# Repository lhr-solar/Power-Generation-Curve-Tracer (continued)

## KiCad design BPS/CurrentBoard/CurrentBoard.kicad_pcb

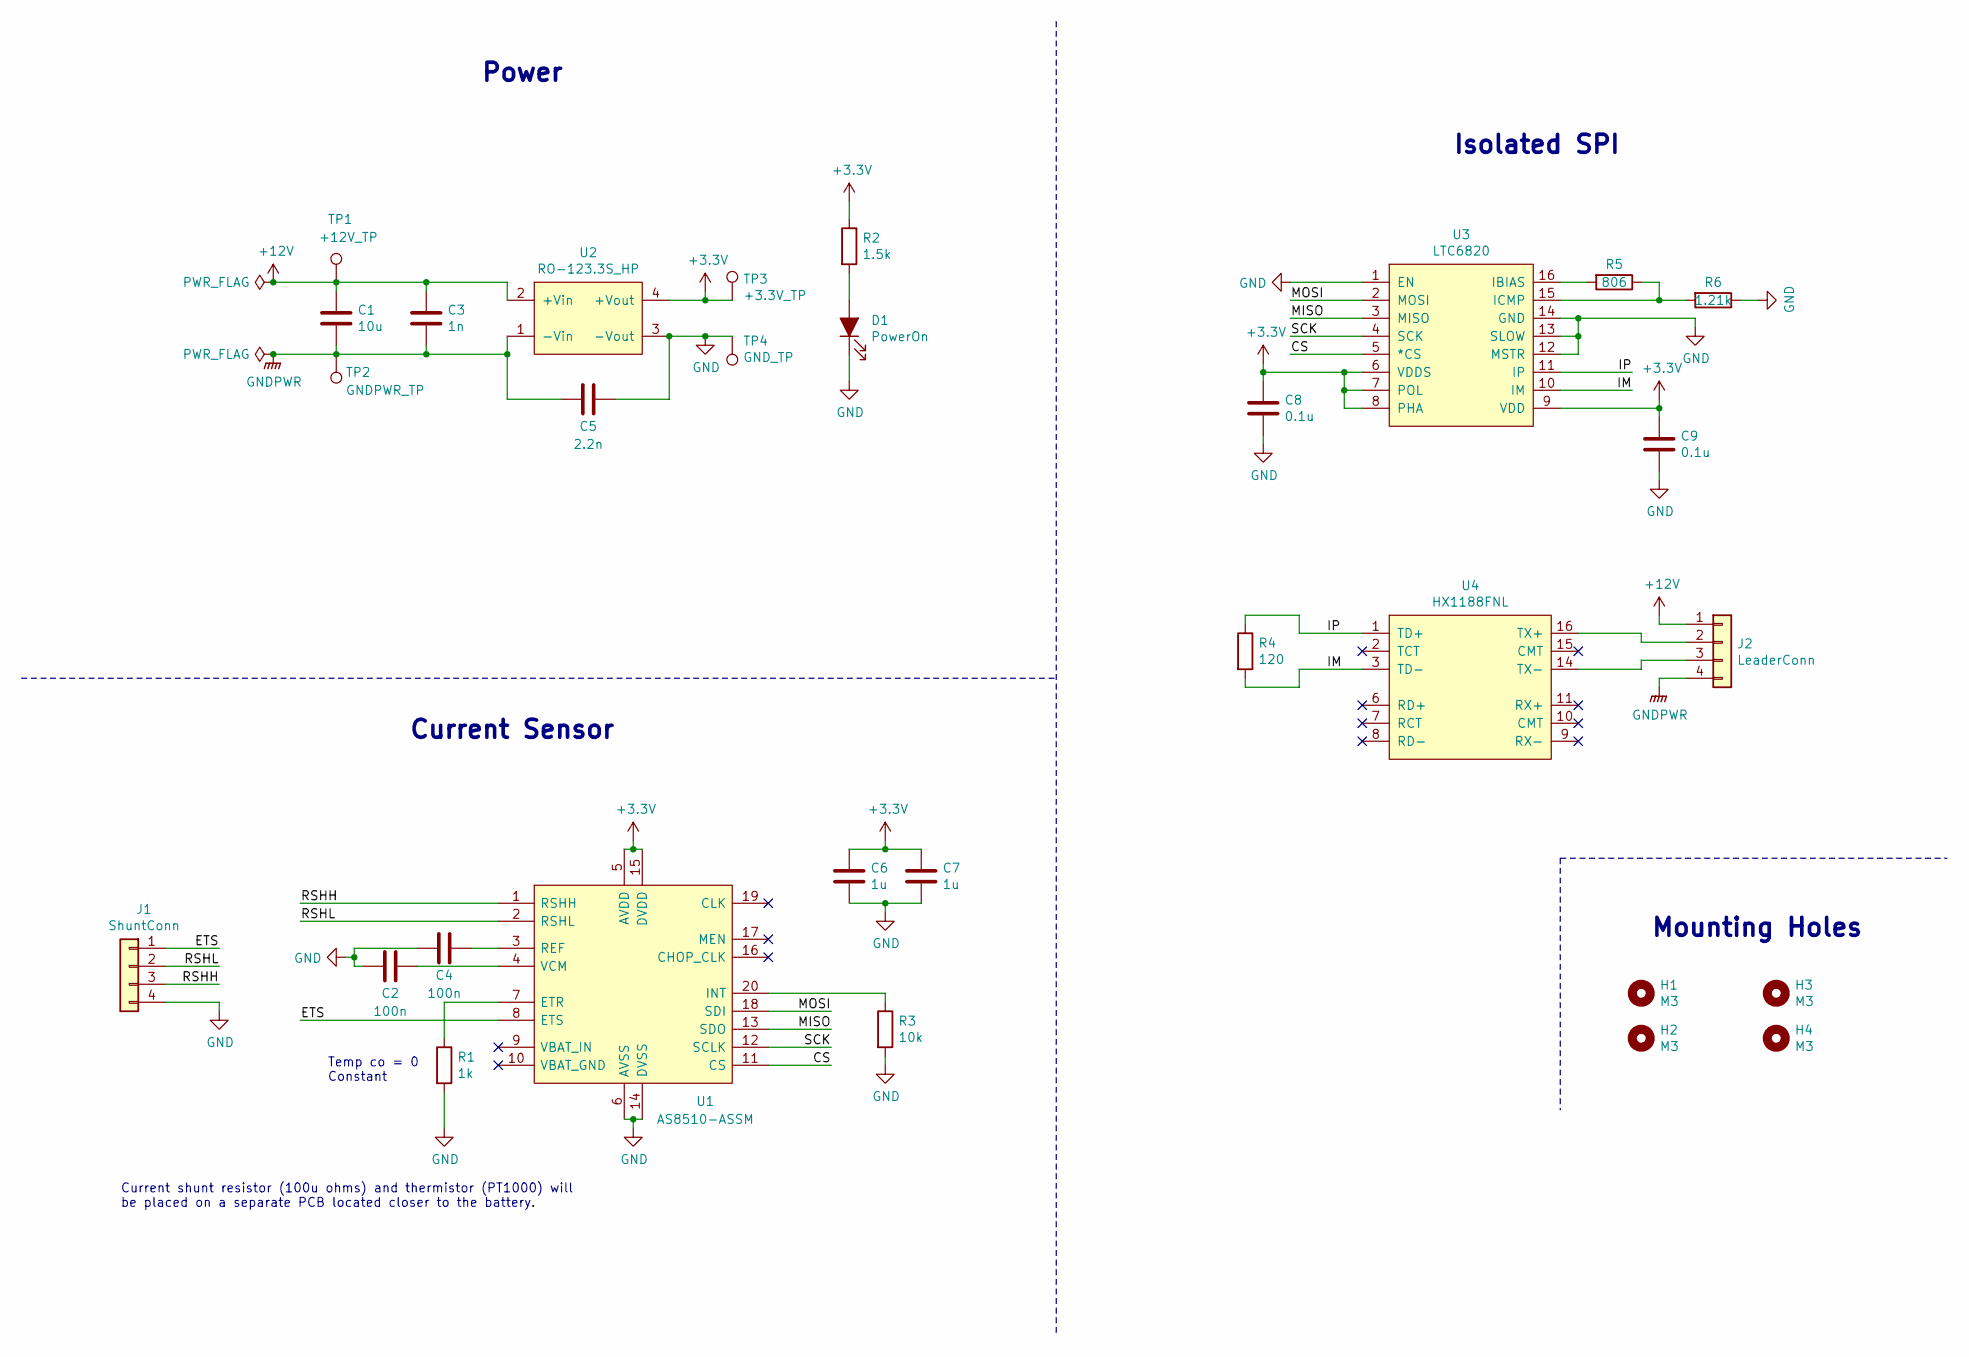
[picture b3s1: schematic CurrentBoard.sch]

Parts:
C1: 10u; C_2220_5750Metrix
C2, C4: 100n; C_0805_2012Metric
C3: 1n; C_0805_2012Metric
C5: 2.2n; C_0805_2012Metric
C6, C7: 1u; C_0805_2012Metric
C8, C9: 0.1u; C_0805_2012Metric
D1: PowerOn; LED_0805_2012Metric
H1, H2, H3, H4: M3; MountingHole_3mm
J1: ShuntConn; Molex_Micro-Fit_3.0_43650-0415_1x04_P3.00mm_Vertical
J2: LeaderConn; Molex_Micro-Fit_3.0_43650-0415_1x04_P3.00mm_Vertical
R1: 1k; R_0805_2012Metric
R2: 1.5k; R_0805_2012Metric
R3: 10k; R_0805_2012Metric
R4: 120; R_0805_2012Metric
R5: 806; R_0805_2012Metric
R6: 1.21k; R_0805_2012Metric
TP1: +12V_TP; TestPoint_Keystone_5005-5009_Compact
TP2: GNDPWR_TP; TestPoint_Keystone_5005-5009_Compact
TP3: +3.3V_TP; TestPoint_Keystone_5005-5009_Compact
TP4: GND_TP; TestPoint_Keystone_5005-5009_Compact
U1: AS8510-ASSM; Manufacturer_Part_Number AS8510-ASSM; Mouser Part Number 985-AS8510-ASSM
U2: RO-123.3S_HP; RI3_DC_Converter
U3: LTC6820; MSOP-16_3x4mm_P0.5mm
U4: HX1188FNL; HXXXX

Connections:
+3V3: C6.1, C7.1, C8.1, C9.1, R2.1, TP3.1, U1.5 (AVDD), U1.15 (DVDD), U2.4 (+Vout), U3.6 (VDDS), U3.7 (POL), U3.8 (PHA), U3.9 (VDD)
+12V: C1.1, C3.1, J2.1, TP1.1, U2.2 (+Vin)
/CS: U1.11 (CS), U3.5 (*CS)
/ETS: J1.1, U1.8 (ETS)
/IM: R4.2, U3.10 (IM), U4.3 (TD-)
/IP: R4.1, U3.11 (IP), U4.1 (TD+)
/MISO: U1.13 (SDO), U3.3 (MISO)
/MOSI: U1.18 (SDI), U3.2 (MOSI)
/RSHH: J1.3, U1.1 (RSHH)
/RSHL: J1.2, U1.2 (RSHL)
/SCK: U1.12 (SCLK), U3.4 (SCK)
GND: C2.2, C4.1, C5.2, C6.2, C7.2, C8.2, C9.2, D1.1 (K), J1.4, R1.2, R3.2, R6.1, TP4.1, U1.6 (AVSS), U1.14 (DVSS), U2.3 (-Vout), U3.1 (EN), U3.12 (MSTR), U3.13 (SLOW), U3.14 (GND)
GNDPWR: C1.2, C3.2, C5.1, J2.4, TP2.1, U2.1 (-Vin)
unnamed: C2.1, U1.4 (VCM)
unnamed: C4.2, U1.3 (REF)
unnamed: D1.2 (A), R2.2
unnamed: J2.2, U4.16 (TX+)
unnamed: J2.3, U4.14 (TX-)
unnamed: R1.1, U1.7 (ETR)
unnamed: R3.1, U1.20 (INT)
unnamed: R5.1, R6.2, U3.15 (ICMP)
unnamed: R5.2, U3.16 (IBIAS)

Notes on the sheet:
Current shunt resistor (100u ohms) and thermistor (PT1000) will be placed on a separate PCB located closer to the battery.
Temp co = 0 Constant
Isolated SPI
Current Sensor
Mounting Holes
Power

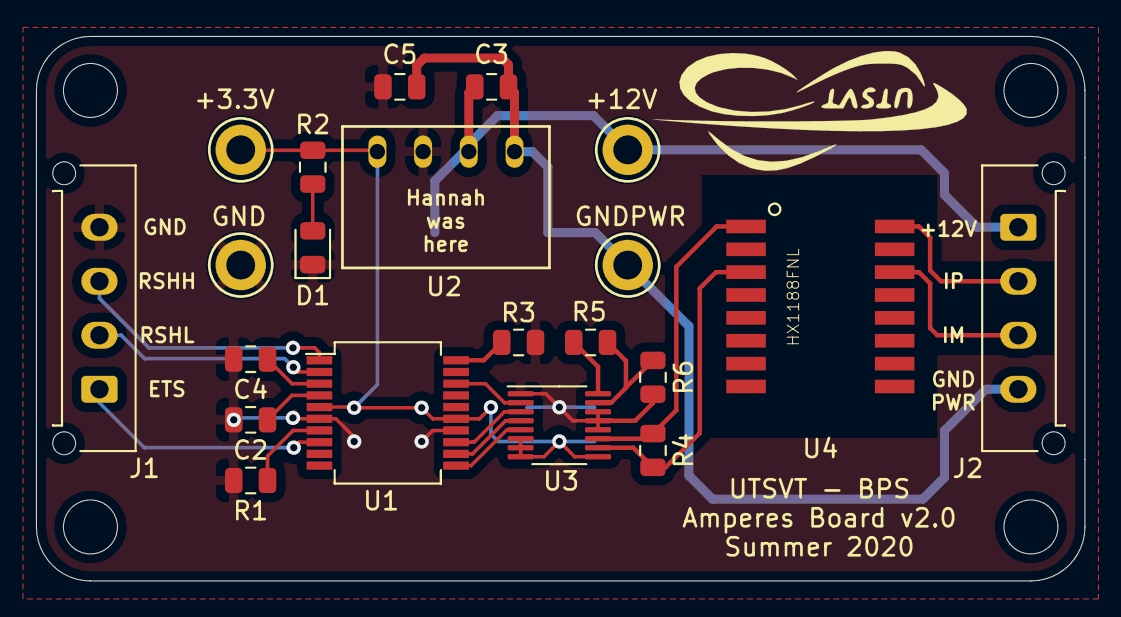
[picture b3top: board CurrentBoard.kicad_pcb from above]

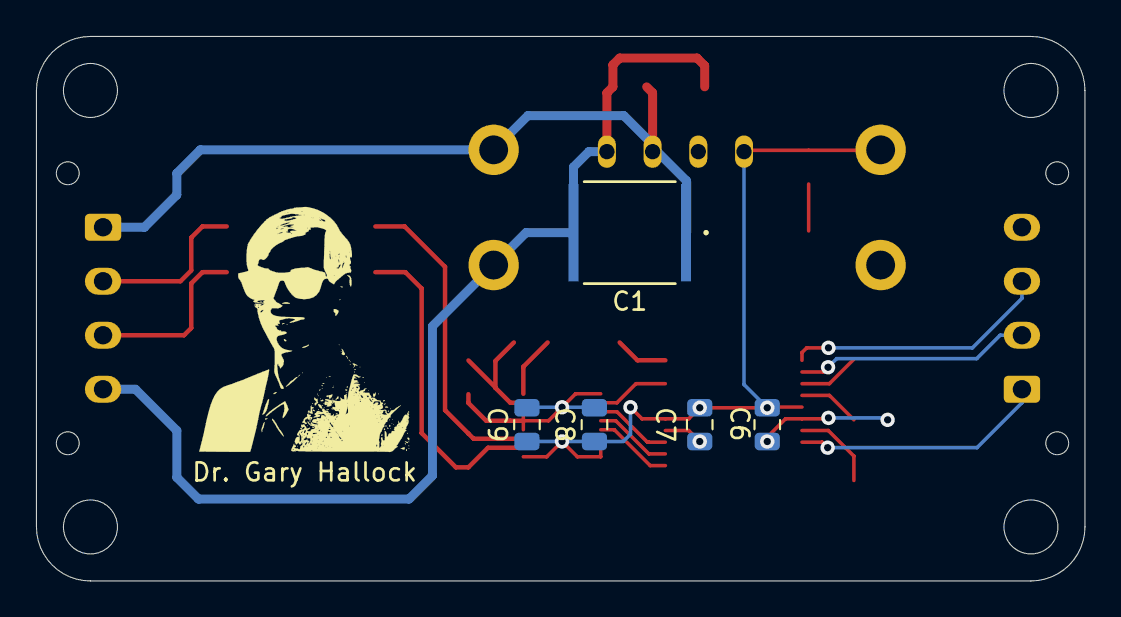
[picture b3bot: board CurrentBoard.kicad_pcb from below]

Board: 2 copper layers, 58.2 x 30.2 mm, 30 parts (5 on the bottom side), 22 nets.

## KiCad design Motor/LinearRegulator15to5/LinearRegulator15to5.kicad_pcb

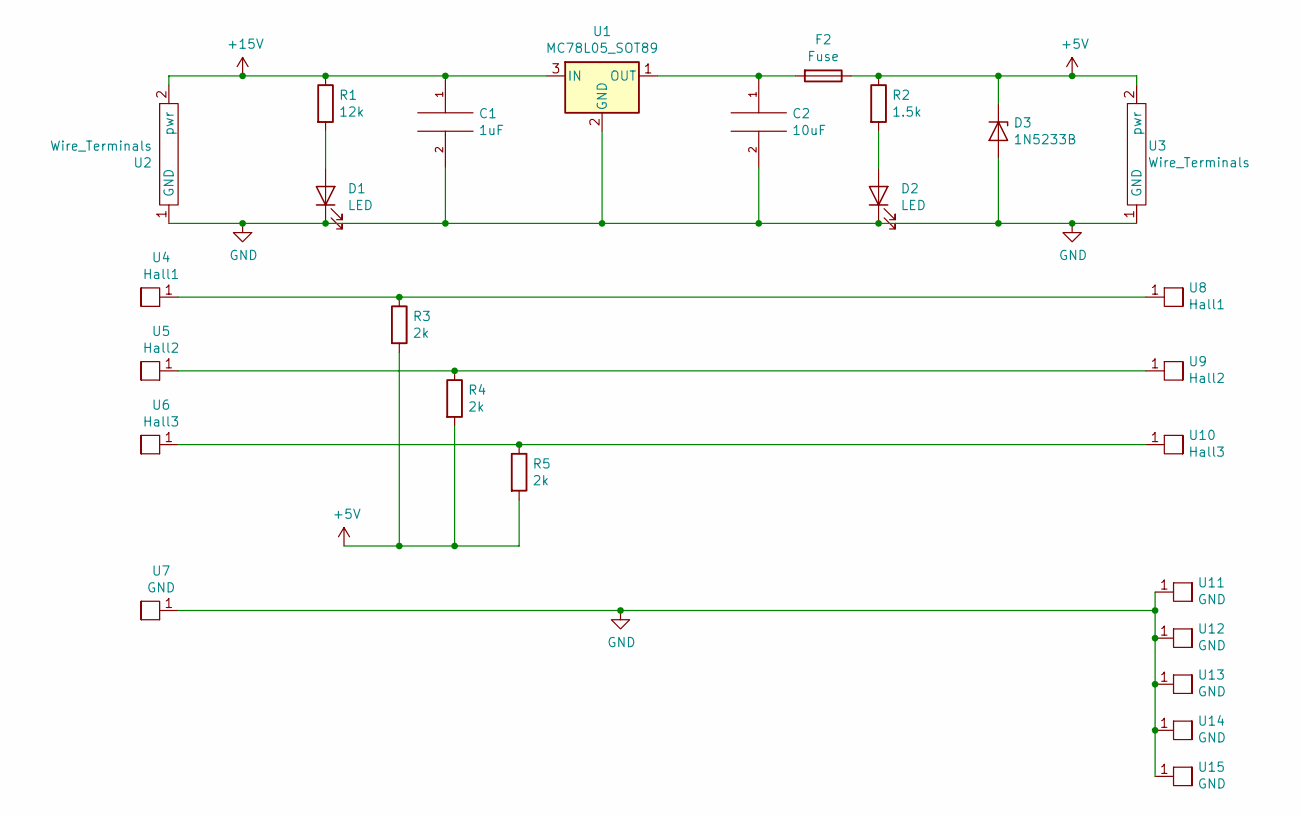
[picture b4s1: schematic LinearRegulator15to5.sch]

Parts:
C1: 1uF; C_0805_2012Metric_Pad1.15x1.40mm_HandSolder
C2: 10uF; C_0805_2012Metric_Pad1.15x1.40mm_HandSolder
D1, D2: LED; D_0805_2012Metric_Pad1.15x1.40mm_HandSolder
D3: 1N5233B; D_DO-35_SOD27_P5.08mm_Vertical_AnodeUp
F2: Fuse; BK_PCB-1_2-R
R1: 12k; R_0805_2012Metric_Pad1.15x1.40mm_HandSolder
R2: 1.5k; R_0805_2012Metric_Pad1.15x1.40mm_HandSolder
R3, R4, R5: 2k; R_0805_2012Metric
U1: MC78L05_SOT89; SOT-89-3
U2, U3: Wire_Terminals; wire_terminals
U4, U8: Hall1; Pad
U5, U9: Hall2; Pad
U6, U10: Hall3; Pad
U7, U11, U12, U13, U14, U15: GND; Pad

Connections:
+5V: D3.1 (K), F2.1, R2.1, R3.2, R4.2, R5.2, U3.2 (pwr)
+15V: C1.1, R1.1, U1.3 (IN), U2.2 (pwr)
GND: C1.2, C2.2, D1.1 (K), D2.1 (K), D3.2 (A), U1.2 (GND), U2.1 (GND), U3.1 (GND), U7.1, U11.1, U12.1, U13.1, U14.1, U15.1
unnamed: C2.1, F2.2, U1.1 (OUT)
unnamed: D1.2 (A), R1.2
unnamed: D2.2 (A), R2.2
unnamed: R3.1, U4.1, U8.1
unnamed: R4.1, U5.1, U9.1
unnamed: R5.1, U6.1, U10.1

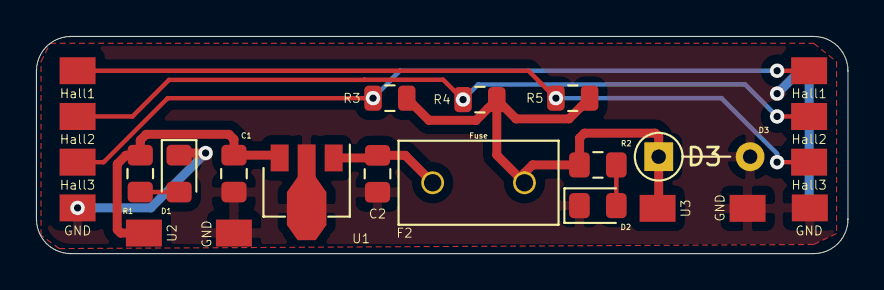
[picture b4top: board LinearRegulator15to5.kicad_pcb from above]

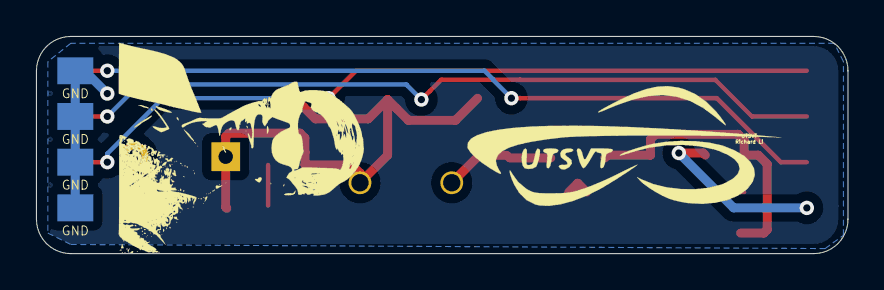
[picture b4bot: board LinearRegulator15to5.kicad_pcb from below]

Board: 2 copper layers, 45.1 x 12.1 mm, 26 parts (4 on the bottom side), 9 nets.

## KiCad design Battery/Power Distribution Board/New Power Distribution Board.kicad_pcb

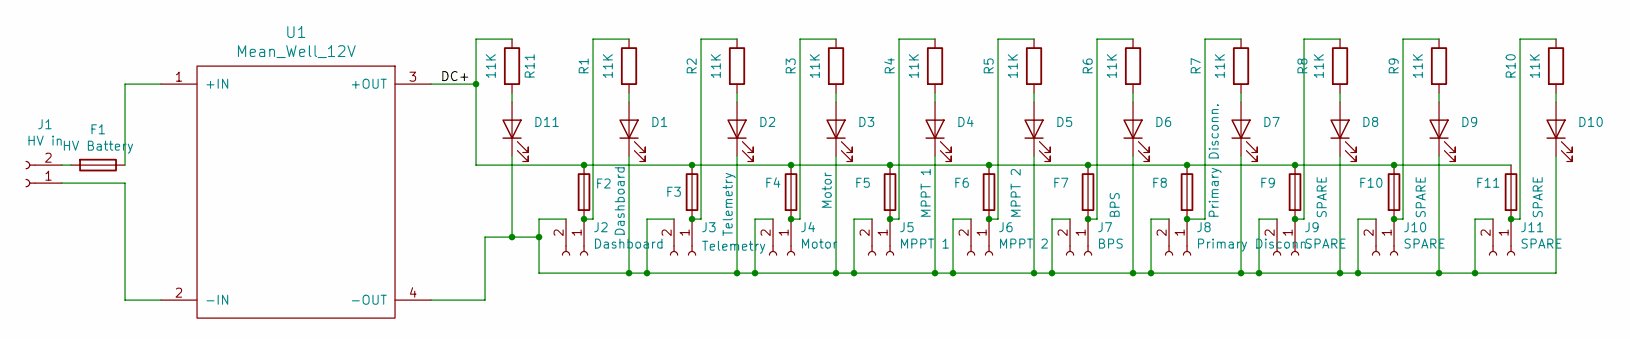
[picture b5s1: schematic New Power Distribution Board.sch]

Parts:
D1, D2, D3, D4, D5, D6, D7, D8, D9, D10, D11: LED; LED_D3.0mm
F1: HV Battery; Fuseholder_Cylinder-5x20mm_Schurter_0031_8201_Horizontal_Op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
F2: Dashboard; Fuseholder_Blade_Mini_Keystone_3568
F3: Telemetry; Fuseholder_Blade_Mini_Keystone_3568
F4: Motor; Fuseholder_Blade_Mini_Keystone_3568
F5: MPPT 1; Fuseholder_Blade_Mini_Keystone_3568
F6: MPPT 2; Fuseholder_Blade_Mini_Keystone_3568
F7: BPS; Fuseholder_Blade_Mini_Keystone_3568
F8: Primary Disconn.; Fuseholder_Blade_Mini_Keystone_3568
F9, F10, F11: SPARE; Fuseholder_Blade_Mini_Keystone_3568
J1: HV in; PhoenixContact_PC_2-GF_2x7.62
J2: Dashboard; Molex_Micro-Fit_3.0_43650-0215_1x02_P3.00mm_Vertical
J3: Telemetry; Molex_Micro-Fit_3.0_43650-0215_1x02_P3.00mm_Vertical
J4: Motor; Molex_Micro-Fit_3.0_43650-0215_1x02_P3.00mm_Vertical
J5: MPPT 1; Molex_Micro-Fit_3.0_43650-0215_1x02_P3.00mm_Vertical
J6: MPPT 2; Molex_Micro-Fit_3.0_43650-0215_1x02_P3.00mm_Vertical
J7: BPS; Molex_Micro-Fit_3.0_43650-0215_1x02_P3.00mm_Vertical
J8: Primary Disconn.; Molex_Micro-Fit_3.0_43650-0215_1x02_P3.00mm_Vertical
J9, J10, J11: SPARE; Molex_Micro-Fit_3.0_43650-0215_1x02_P3.00mm_Vertical
R1, R2, R3, R4, R5, R6, R7, R8, R9, R10, R11: 11K; R_Axial_DIN0204_L3.6mm_D1.6mm_P7.62mm_Horizontal
U1: Mean_Well_12V; DC-DC Converter 12V

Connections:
/DC+: F2.1, F3.1, F4.1, F5.1, F6.1, F7.1, F8.1, F9.1, F10.1, F11.1, R11.1, U1.3 (+OUT)
unnamed: D1.1 (K), D2.1 (K), D3.1 (K), D4.1 (K), D5.1 (K), D6.1 (K), D7.1 (K), D8.1 (K), D9.1 (K), D10.1 (K), D11.1 (K), J2.2, J3.2, J4.2, J5.2, J6.2, J7.2, J8.2, J9.2, J10.2, J11.2, U1.4 (-OUT)
unnamed: D1.2 (A), R1.2
unnamed: D2.2 (A), R2.2
unnamed: D3.2 (A), R3.2
unnamed: D4.2 (A), R4.2
unnamed: D5.2 (A), R5.2
unnamed: D6.2 (A), R6.2
unnamed: D7.2 (A), R7.2
unnamed: D8.2 (A), R8.2
unnamed: D9.2 (A), R9.2
unnamed: D10.2 (A), R10.2
unnamed: D11.2 (A), R11.2
unnamed: F1.1, U1.1 (+IN)
unnamed: F1.2, J1.2
unnamed: F2.2, J2.1, R1.1
unnamed: F3.2, J3.1, R2.1
unnamed: F4.2, J4.1, R3.1
unnamed: F5.2, J5.1, R4.1
unnamed: F6.2, J6.1, R5.1
unnamed: F7.2, J7.1, R6.1
unnamed: F8.2, J8.1, R7.1
unnamed: F9.2, J9.1, R8.1
unnamed: F10.2, J10.1, R9.1
unnamed: F11.2, J11.1, R10.1
unnamed: J1.1, U1.2 (-IN)

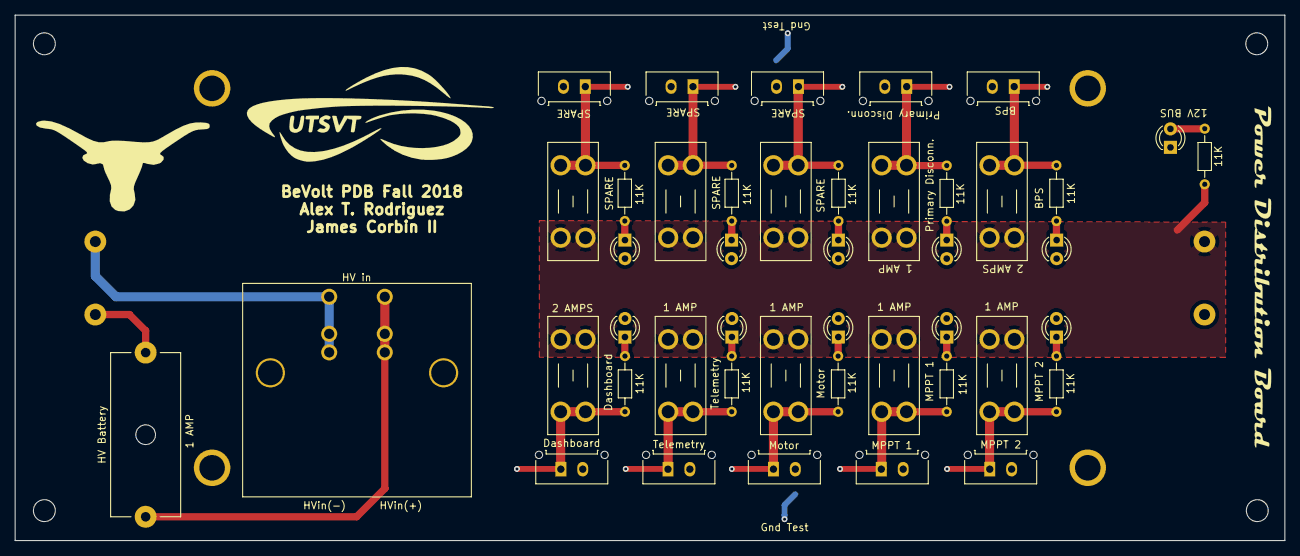
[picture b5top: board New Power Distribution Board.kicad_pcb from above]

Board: 2 copper layers, 174.0 x 72.0 mm, 45 parts (1 on the bottom side), 26 nets.

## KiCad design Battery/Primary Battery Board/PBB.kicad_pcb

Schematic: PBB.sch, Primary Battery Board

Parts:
D1, D2, D3: 1N4001; D_DO-41_SOD81_P10.16mm_Horizontal
D4, D5, D6: SB5100-T; D_DO-201AD_P12.70mm_Horizontal
DS1: PrimBattOn; LED_D3.0mm
DS2: PRIM DSCNCT ON; LED_D3.0mm
DS3: BPS MAIN SUPPLY ON; LED_D3.0mm
DS4: JUMP START ON; LED_D3.0mm
DS5: HORN ON; LED_D3.0mm
DS6: FAN ON; LED_D3.0mm
DS7: RADIOS +12V; LED_D3.0mm
DS8: BPS +12V; LED_D3.0mm
F1: 7.5 AMPS; Fuseholder_Blade_Mini_Keystone_3568
F2: 5 AMPS; Fuseholder_Blade_Mini_Keystone_3568
F3: 2 AMP; Fuseholder_Blade_Mini_Keystone_3568
F4: 2 AMPS; Fuseholder_Blade_Mini_Keystone_3568
J1: Primary Battery +12VDC; Molex_Sabre_43160-0102_1x02_P7.49mm_Vertical
J2: PRIM BATT DISCNCT; Molex_Micro-Fit_3.0_43650-0215_1x02_P3.00mm_Vertical
J3: BPS MAIN SUPPLY; Molex_Micro-Fit_3.0_43650-0215_1x02_P3.00mm_Vertical
J4: JUMP START; Molex_Micro-Fit_3.0_43650-0215_1x02_P3.00mm_Vertical
J5: DashBoard HORN CTL; Molex_Micro-Fit_3.0_43650-0215_1x02_P3.00mm_Vertical
J6: DashBoard DRV FAN CTL; Molex_Micro-Fit_3.0_43650-0215_1x02_P3.00mm_Vertical
J7: HORN +12V; Molex_Micro-Fit_3.0_43650-0215_1x02_P3.00mm_Vertical
J8: DRIVER FAN +12V; Molex_Micro-Fit_3.0_43650-0215_1x02_P3.00mm_Vertical
J9: RADIOS +12V; Molex_Micro-Fit_3.0_43650-0215_1x02_P3.00mm_Vertical
J10: BPS +12V; Molex_Micro-Fit_3.0_43650-0215_1x02_P3.00mm_Vertical
K1, K2, K3: G5Q-1; Relay_SPDT_Omron-G5Q-1
R1, R2, R3, R4, R5, R6, R7, R8: 11K; R_Axial_DIN0204_L3.6mm_D1.6mm_P7.62mm_Horizontal
SW1: Batt Check; SW_Tactile_Straight_KSA0Axx1LFTR
SW2: BPS PWR CHECK; SW_Tactile_Straight_KSA0Axx1LFTR
SW3: RADIO PWR CHECK; SW_Tactile_Straight_KSA0Axx1LFTR
TP1: PRIMBATTVOLTS; TestPoint_Pad_2.0x2.0mm
TP2: PRIMBATTDSCNCT; TestPoint_Pad_2.0x2.0mm
TP3: BPS MAIN MAIN SUPPLY; TestPoint_Pad_2.0x2.0mm
TP4: JUMP START VOLTS; TestPoint_Pad_2.0x2.0mm
TP5: HORN ON; TestPoint_Pad_2.0x2.0mm
TP6: FAN ON; TestPoint_Pad_2.0x2.0mm
TP7: RADIO PWR; TestPoint_Pad_2.0x2.0mm
TP8: BPS SUPPLY VOLTS; TestPoint_Pad_2.0x2.0mm

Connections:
GNDS: D3.2, DS1.1, DS2.1, DS3.1, DS4.1, DS5.1, DS6.1, DS7.1, DS8.1, J1.2, J2.2, J3.2, J4.2, J5.2, J6.2, J7.2, J8.2, J9.2, J10.2, K3.1; also elsewhere on the board
unnamed: D1.1, F1.2, K1.3, K1.5
unnamed: D1.2, J5.1, K1.1
unnamed: D2.1, F2.2, K2.3, K2.5
unnamed: D2.2, J6.1, K2.1
unnamed: D3.1, J2.1, K3.5, R2.1, TP2.1
unnamed: D4.1 (K), D5.1 (K), D6.1 (K), J10.1, SW2.2, TP8.1
unnamed: D4.2 (A), K3.2
unnamed: D5.2 (A), J3.1, R3.1, TP3.1
unnamed: D6.2 (A), J4.1, R4.1, TP4.1
unnamed: DS1.2, R1.2
unnamed: DS2.2, R2.2
unnamed: DS3.2, R3.2
unnamed: DS4.2, R4.2
unnamed: DS5.2, R5.2
unnamed: DS6.2, R6.2
unnamed: DS7.2, R7.2
unnamed: DS8.2, R8.2
unnamed: F1.1, F2.1, F3.1, F4.1, J1.1, SW1.2, TP1.1
unnamed: F3.2, J9.1, SW3.2, TP7.1
unnamed: F4.2, K3.4
unnamed: J7.1, K1.2, R5.1, TP5.1
unnamed: J8.1, K2.2, R6.1, TP6.1
unnamed: R1.1, SW1.1
unnamed: R7.1, SW3.1
unnamed: R8.1, SW2.1

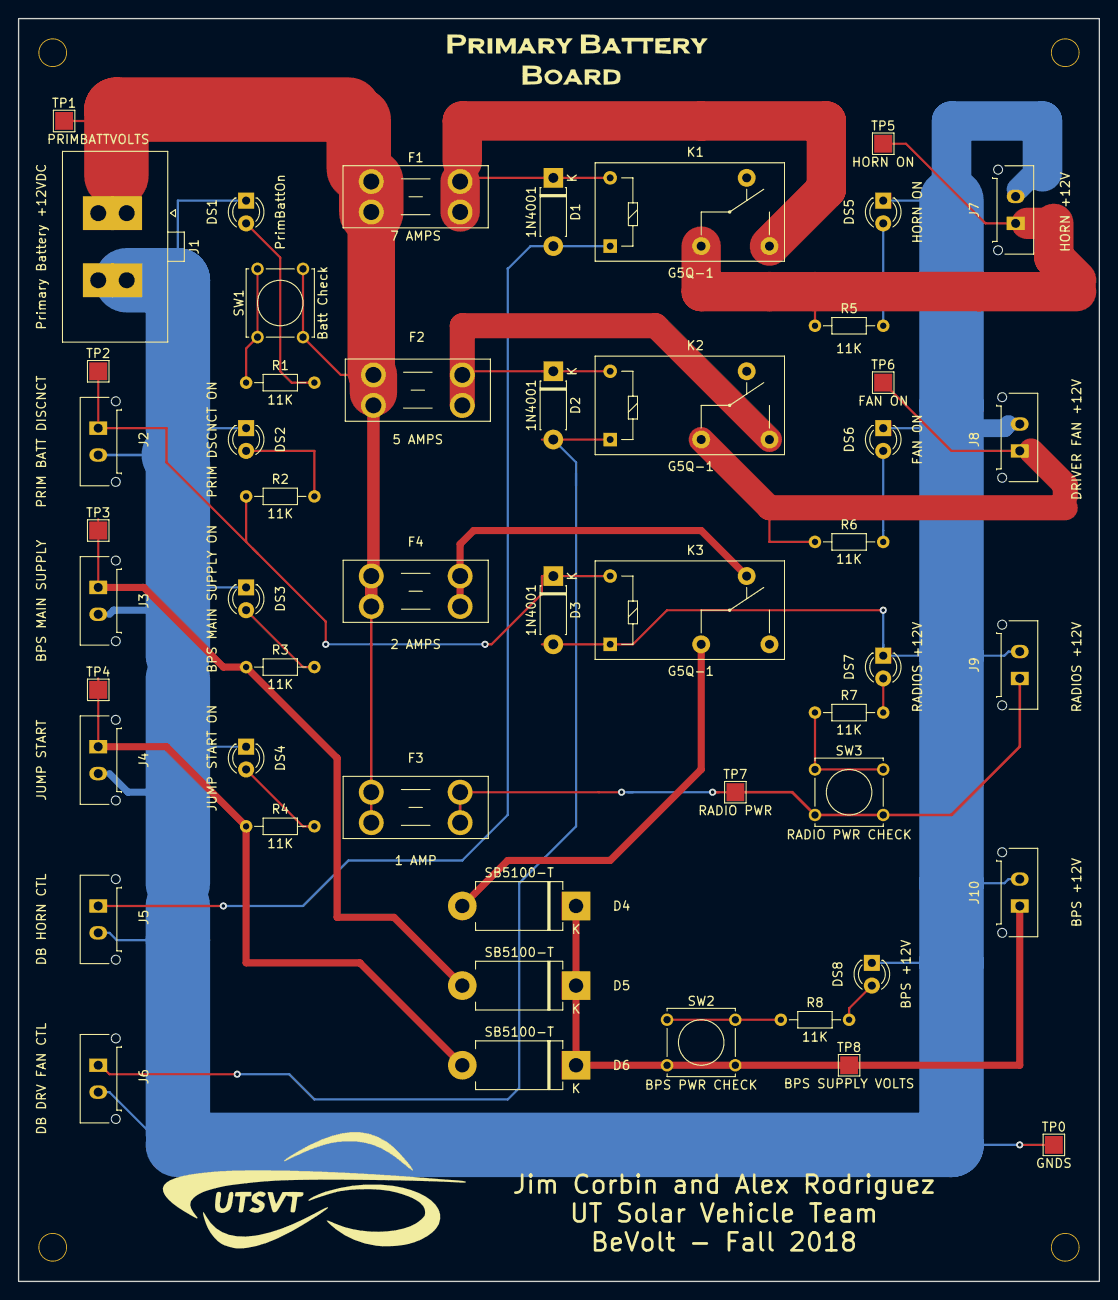
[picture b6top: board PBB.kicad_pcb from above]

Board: 2 copper layers, 120.7 x 141.0 mm, 51 parts (0 on the bottom side), 26 nets.

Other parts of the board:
TP0: GNDS; TestPoint_Pad_2.0x2.0mm

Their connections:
GNDS: TP0.1; also elsewhere on the board

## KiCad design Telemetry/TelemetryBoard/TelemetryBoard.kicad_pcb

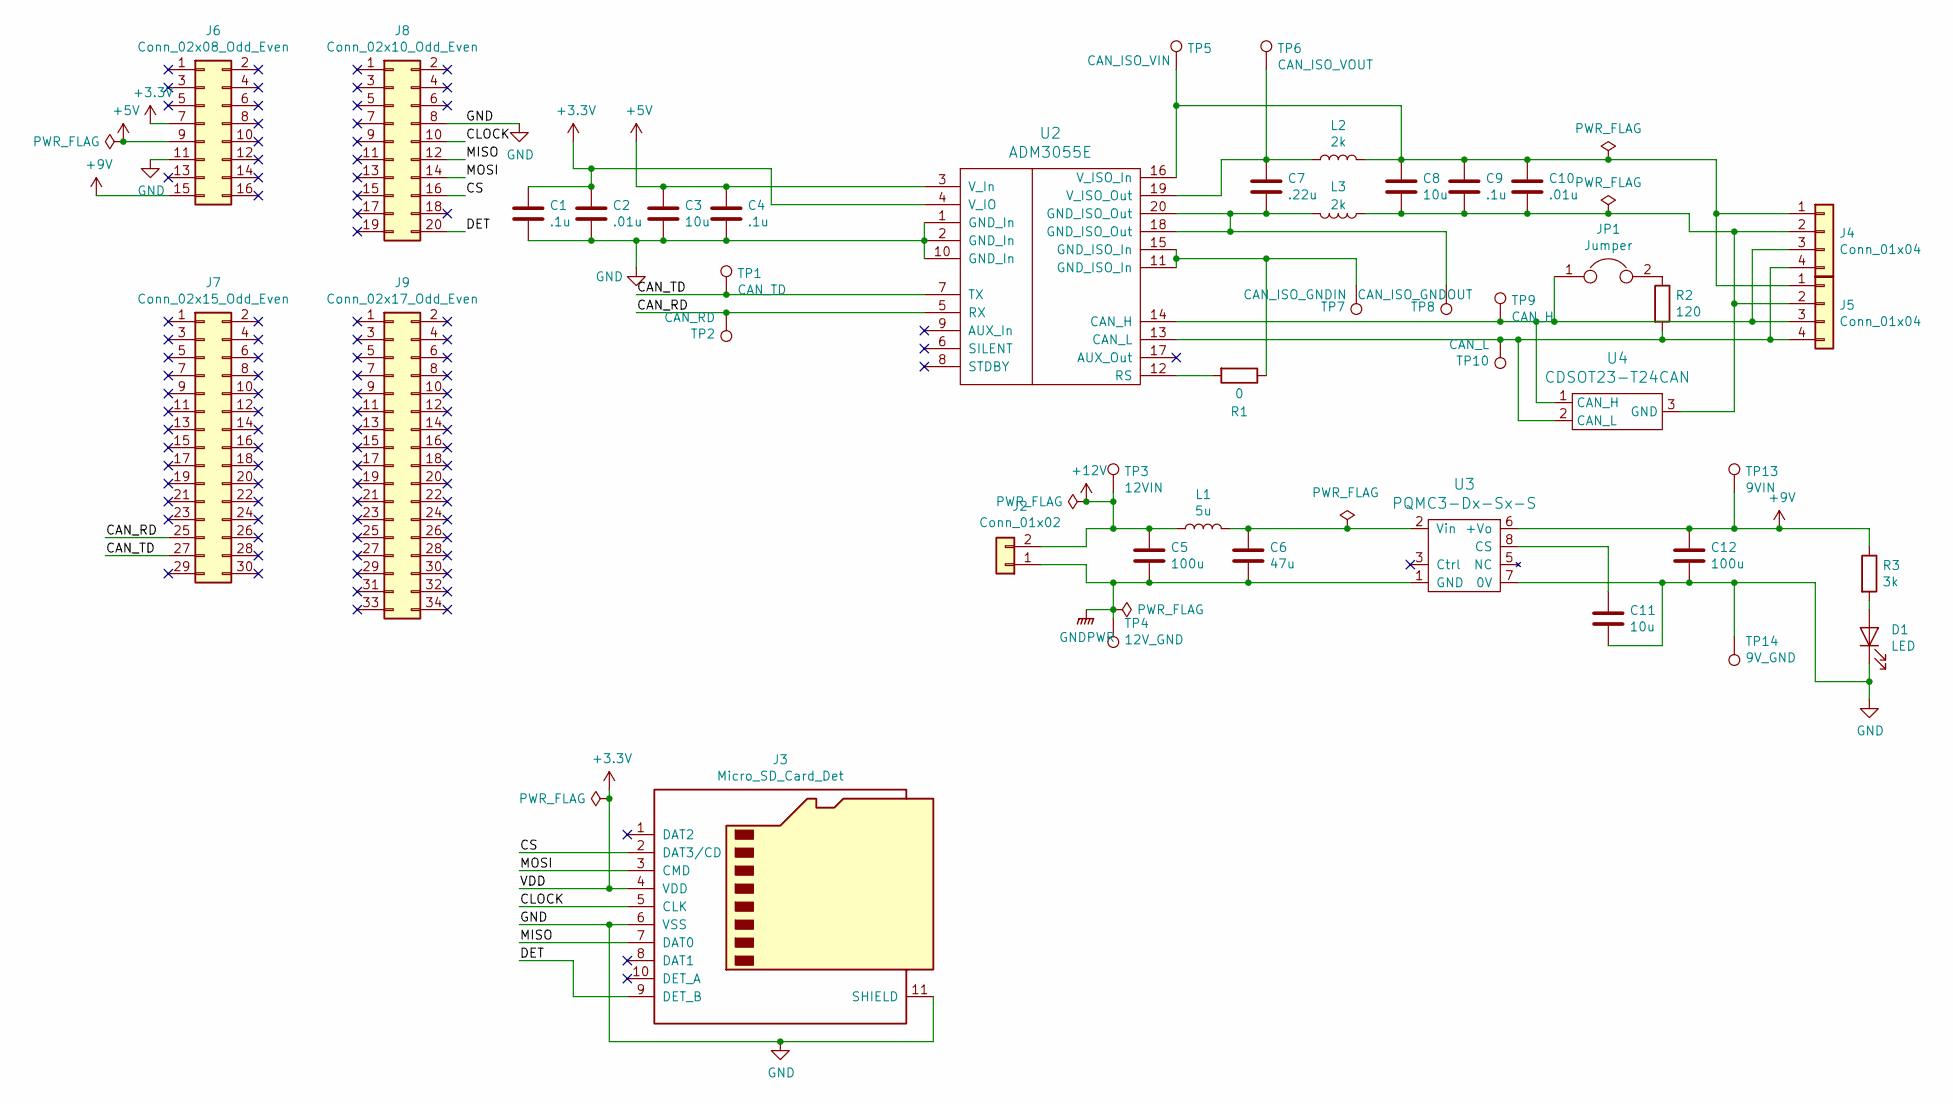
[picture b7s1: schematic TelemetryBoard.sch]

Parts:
C1, C4, C9: .1u; C_0805_2012Metric
C2, C10: .01u; C_0805_2012Metric
C3, C8, C11: 10u; C_0805_2012Metric
C5, C12: 100u; C_0805_2012Metric
C6: 47u; C_0805_2012Metric
C7: .22u; C_0805_2012Metric
D1: LED; LED_0805_2012Metric
J2: Conn_01x02; Molex_Micro-Fit_3.0_43650-0215_1x02_P3.00mm_Vertical
J3: Micro_SD_Card_Det; microSD_HC_Hirose_DM3AT-SF-PEJM5
J4, J5: Conn_01x04; Molex_Micro-Fit_3.0_43650-0415_1x04_P3.00mm_Vertical
J6: Conn_02x08_Odd_Even; PinHeader_2x08_P2.54mm_Vertical
J7: Conn_02x15_Odd_Even; PinHeader_2x15_P2.54mm_Vertical
J8: Conn_02x10_Odd_Even; PinHeader_2x10_P2.54mm_Vertical
J9: Conn_02x17_Odd_Even; PinHeader_2x17_P2.54mm_Vertical
JP1: Jumper; PinHeader_1x02_P2.54mm_Vertical
L1: 5u; L_TDK_NLV32_3.2x2.5mm
L2, L3: 2k; L_0805_2012Metric
R1: 0; R_0805_2012Metric
R2: 120; R_0805_2012Metric
R3: 3k; R_0805_2012Metric
TP1: CAN_TD; TestPoint_Keystone_5005-5009_Compact
TP2: CAN_RD; TestPoint_Keystone_5005-5009_Compact
TP3: 12VIN; TestPoint_Keystone_5005-5009_Compact
TP4: 12V_GND; TestPoint_Keystone_5005-5009_Compact
TP5: CAN_ISO_VIN; TestPoint_Keystone_5005-5009_Compact
TP6: CAN_ISO_VOUT; TestPoint_Keystone_5005-5009_Compact
TP7: CAN_ISO_GNDIN; TestPoint_Keystone_5005-5009_Compact
TP8: CAN_ISO_GNDOUT; TestPoint_Keystone_5005-5009_Compact
TP9: CAN_H; TestPoint_Keystone_5005-5009_Compact
TP10: CAN_L; TestPoint_Keystone_5005-5009_Compact
TP13: 9VIN; TestPoint_Keystone_5005-5009_Compact
TP14: 9V_GND; TestPoint_Keystone_5005-5009_Compact
U2: ADM3055E; SOIC-20W_7.5x15.4mm_Pitch1.27mm
U3: PQMC3-Dx-Sx-S; CUI_PQMC3-S
U4: CDSOT23-T24CAN; SOT-23W_Handsoldering

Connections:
+3V3: C1.1, C2.1, J3.4 (VDD), J6.7, U2.4 (V_IO)
+5V: C3.1, C4.1, J6.9, U2.3 (V_In)
+9V: C12.1, J6.15, R3.1, TP13.1, U3.6 (+Vo)
+12V: C5.1, J2.2, L1.1, TP3.1
/CAN_RD: J7.25, TP2.1, U2.5 (RX)
/CAN_TD: J7.27, TP1.1, U2.7 (TX)
/CLOCK: J3.5 (CLK), J8.10
/CS: J3.2 (DAT3/CD), J8.16
/DET: J3.9 (DET_B), J8.20
/MISO: J3.7 (DAT0), J8.12
/MOSI: J3.3 (CMD), J8.14
GND: C1.2, C2.2, C3.2, C4.2, C11.2, C12.2, D1.1 (K), J3.6 (VSS), J3.11 (SHIELD), J6.11, J8.8, TP14.1, U2.1 (GND_In), U2.2 (GND_In), U2.10 (GND_In), U3.7 (0V)
GNDPWR: C5.2, C6.2, J2.1, TP4.1, U3.1 (GND)
unnamed: C6.1, L1.2, U3.2 (Vin)
unnamed: C7.1, L2.1, TP6.1, U2.19 (V_ISO_Out)
unnamed: C7.2, L3.2, TP8.1, U2.18 (GND_ISO_Out), U2.20 (GND_ISO_Out)
unnamed: C8.1, C9.1, C10.1, J4.1, J5.1, L2.2, TP5.1, U2.16 (V_ISO_In)
unnamed: C8.2, C9.2, C10.2, J4.2, J5.2, L3.1, U4.3 (GND)
unnamed: C11.1, U3.8 (CS)
unnamed: D1.2 (A), R3.2
unnamed: J4.3, J5.3, JP1.1, TP9.1, U2.14 (CAN_H), U4.1 (CAN_H)
unnamed: J4.4, J5.4, R2.2, TP10.1, U2.13 (CAN_L), U4.2 (CAN_L)
unnamed: JP1.2, R2.1
unnamed: R1.1, TP7.1, U2.11 (GND_ISO_In), U2.15 (GND_ISO_In)
unnamed: R1.2, U2.12 (RS)

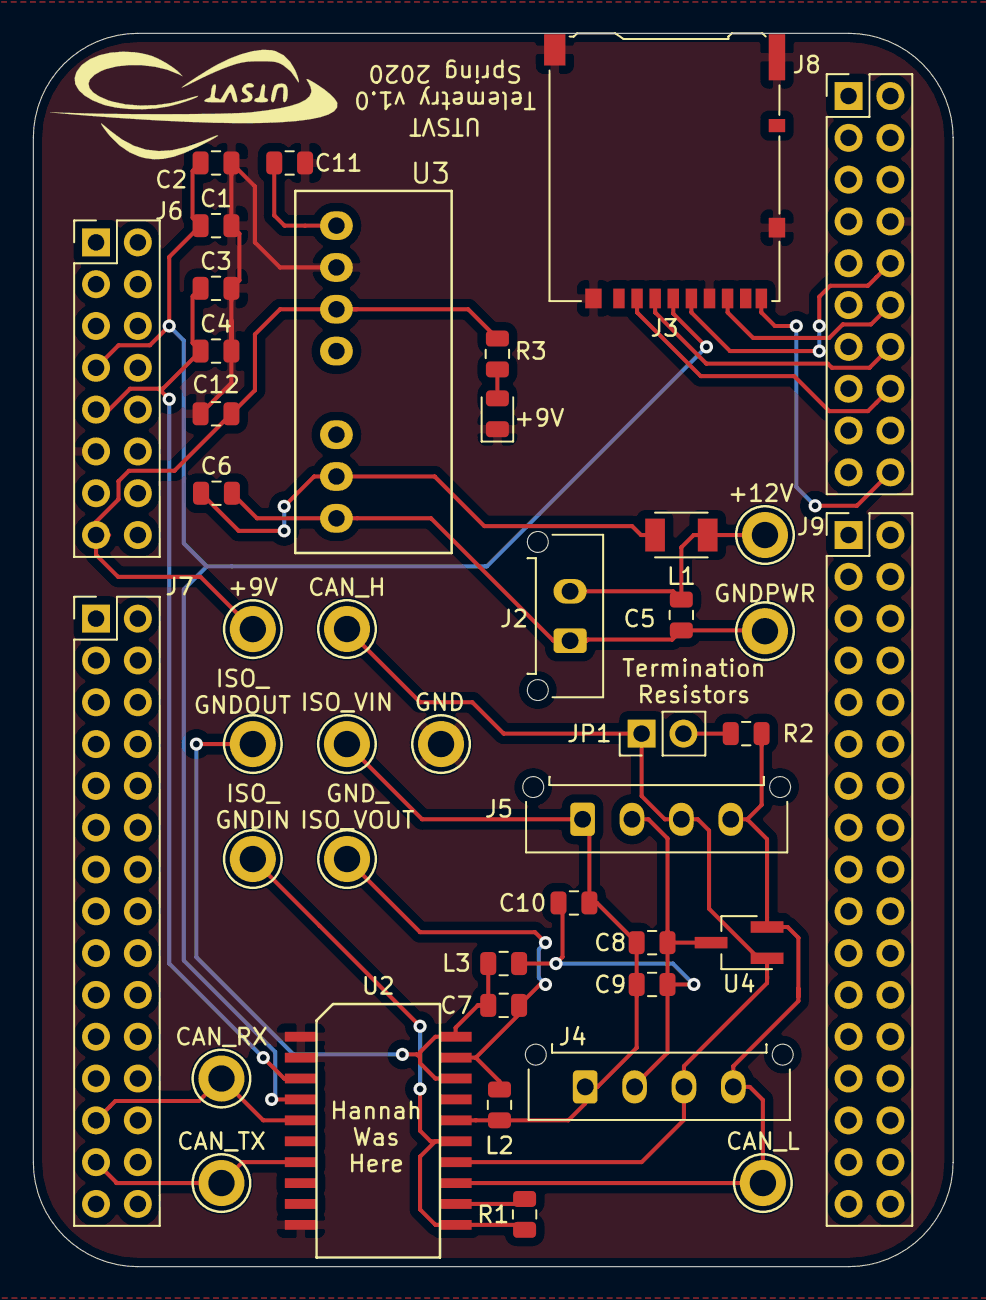
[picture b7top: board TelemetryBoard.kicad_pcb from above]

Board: 2 copper layers, 55.9 x 74.9 mm, 43 parts (0 on the bottom side), 25 nets.
